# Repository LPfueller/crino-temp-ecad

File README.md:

View this project on [CADLAB.io](https://cadlab.io/project/27832). 

# Crino Board - Template (RevB.1.0)

Crino offers precise characterisations of lithium ion cells for quality control in battery manufacturing and research using the *crino instrument*. Every crino instrument consists of several *crino boards* with actuators and sensors that are connected to a central control system (currently a *Raspberry Pi*). This control system is performing all measurements and also provides a user interface to interact with the system. This repository consists of Kicad development files for the *board-template*. All *crino boards* should be derived from this template. 

## Project directory structure

- **docs**: Contains additional documentation of the project.
- **hardware**: Contains the KiCad project.
- **hardware/fab**: Contains automatically generated BOM, and gerber files.
- **simulation**: Contains LTSpice simulations related to this project.

## Local Development Experience

**Prerequisites**:

If you are new to `crino development workflow`, please visit [crino-onboarding](https://github.com/crinolab/crino-onboarding) and [crino-onboarding-ecad](https://github.com/crinolab/crino-onboarding-ecad/tree/master/ecad) first.

**How to use the Template**:

Open Kicad, create a `new Project by Template`. Navigate to the following path and select the *Board Template*. Create a new project with the selected template.

- `<your path>crino-repos/crino-board/ecad/hardware`

In order to update the schematics, the newly created project has to be linked to the template. Use [git submodules](https://git-scm.com/book/en/v2/Git-Tools-Submodules) to link this repository to your task specific crino-board.

- `git submodule add -f https://github.com/crinolab/crino-board.git ./ecad/hardware/crino-board`

If you want to update you task specific crino-board to a new template, use 

- `git submodule update --init --recursive`

Open Kicad again and switch to the schematics of your new project. A block called `mcu` should be visible. Enter the properties dialog and change the *sheet name* to the following path.

- `.\crino-board\ecad\hardware\mcu.sch`

Now the schematics are linked to the template project. Appending all the symbols may be necessary. 

**How to apply changes in the Layout**

in order to apply changes in the Layout. The [KiCad Action Plugins](https://github.com/MitjaNemec/Kicad_action_plugins) have to be installed. Follow the instructions on the website.  

**Workflow for the Plugin (Rev1)**

1. After updating the submodule open the template folder
2. Open the template-layout and select TP14 (Reference Point)
3. `Tools -> External Plugins -> Save/Restore Layout -> Save Layout`
4. Select `mcu.sch` in the window and save `mcu.pckl`
5. Close template layout without saving
6. Open `mcu.pckl` and change Row `5720` 

7. Open project and inspect the schematics
8. Open layout and note position of TP14
9. Delete all footprints and fracks of the template part
10. Start `Update PCB` and place the Footprints anywhere
11. Place TP14 at noted position and select it
12. `Tools -> External Plugins -> Save/Restore Layout -> Restore Layout`
13. Select `mcu.pckl` and wait until completed
14. Start DRC and correct errors
15. Save the Layout
16. Delete `mcu.pckl`

## General Components

The Template is the successor of the previously used [ESP32-POE-ISO](https://www.olimex.com/Products/IoT/ESP32/ESP32-POE-ISO/open-source-hardware). It contains all needed components of the board. 

**Basic Blocks**

The following blocks are present in the schematics:

- `poe` - Power over Ethernet controller
- `power` - Power supply for microcontroller (3.3V, 5V, 12V)
- `esp32` - [Microcontroller](https://www.espressif.com/sites/default/files/documentation/esp32-wroom-32e_esp32-wroom-32ue_datasheet_en.pdf) and programming interface  
- `ethernet` - Ethernet controller
- `io` - Pinout for derived boards

> Before you start making changes, please read the [development workflow](./docs/development-workflow.md) for Crino Power Board.

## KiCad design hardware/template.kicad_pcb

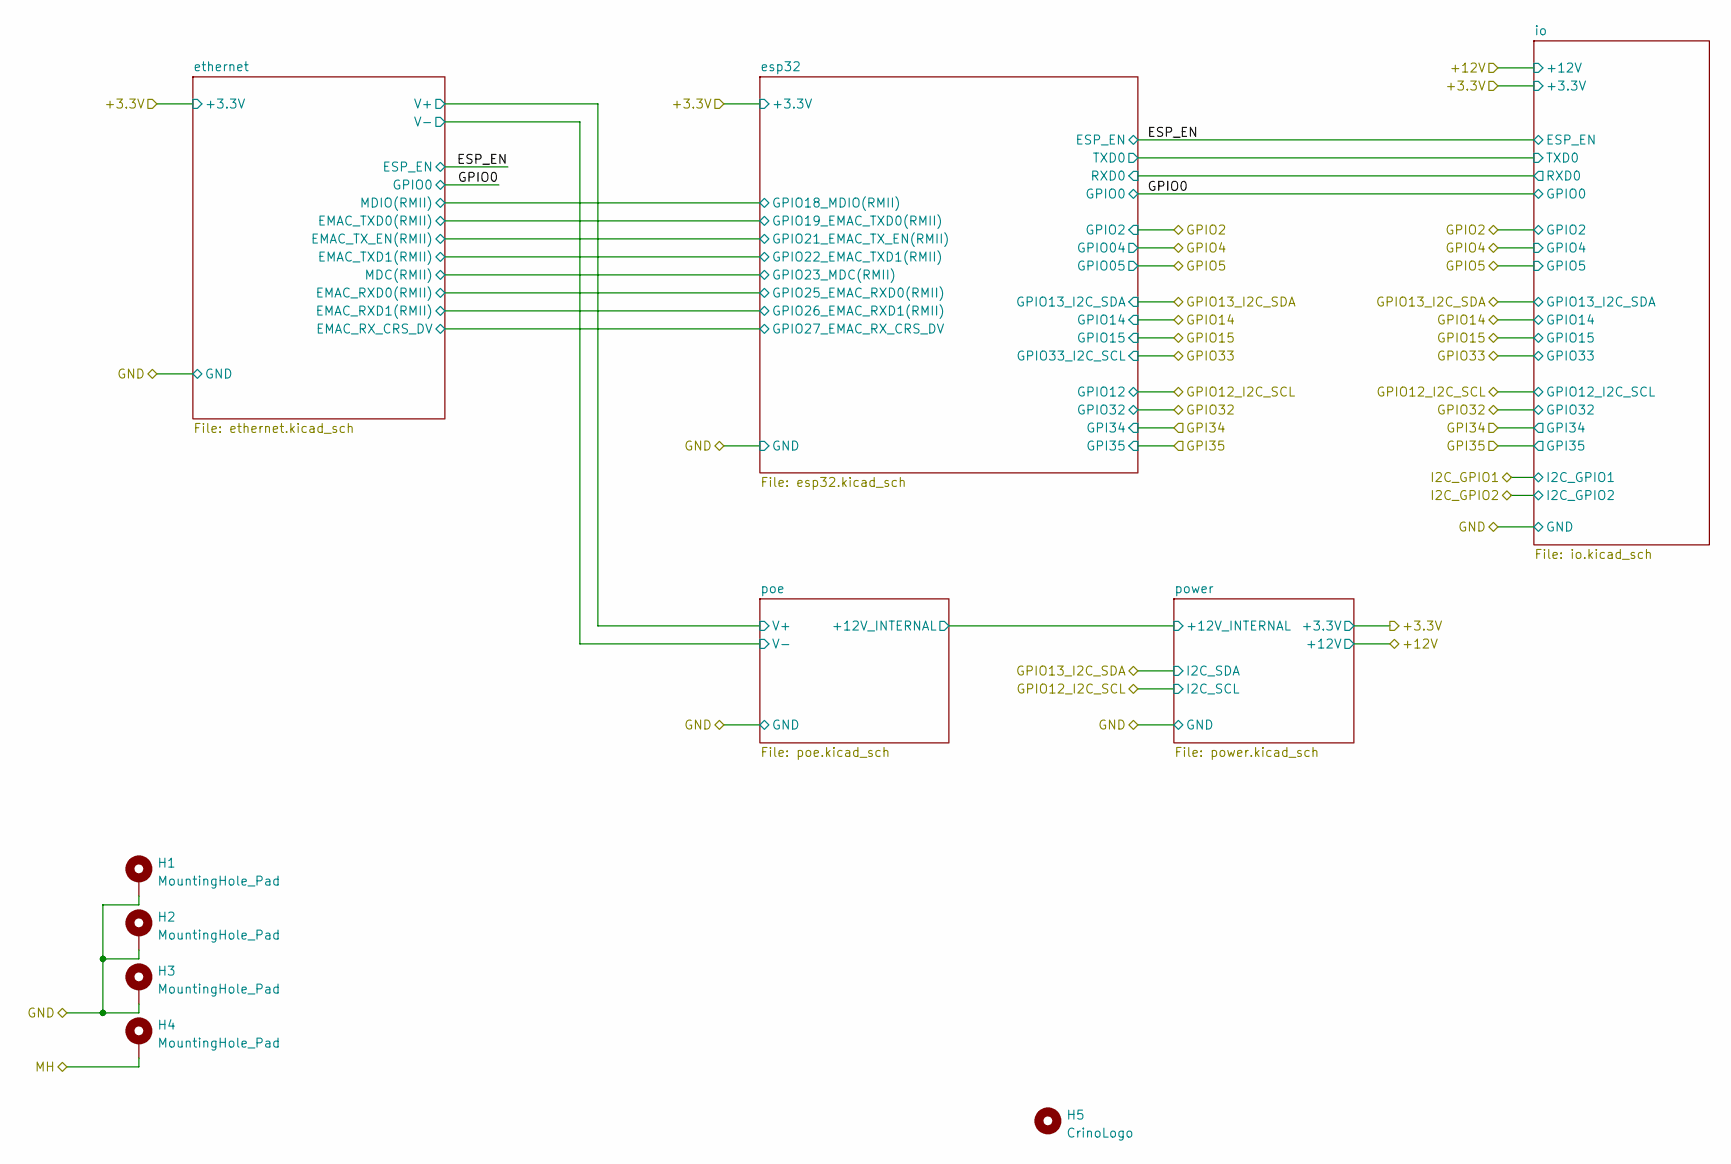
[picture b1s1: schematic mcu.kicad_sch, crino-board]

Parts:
H1, H2, H3, H4: MountingHole_Pad; MountingHole_3.2mm_M3_DIN965_Pad
H5: CrinoLogo; crino_logo

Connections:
/mcu/GND: H1.1, H2.1, H3.1; also elsewhere on the board
/mcu/MH: H4.1

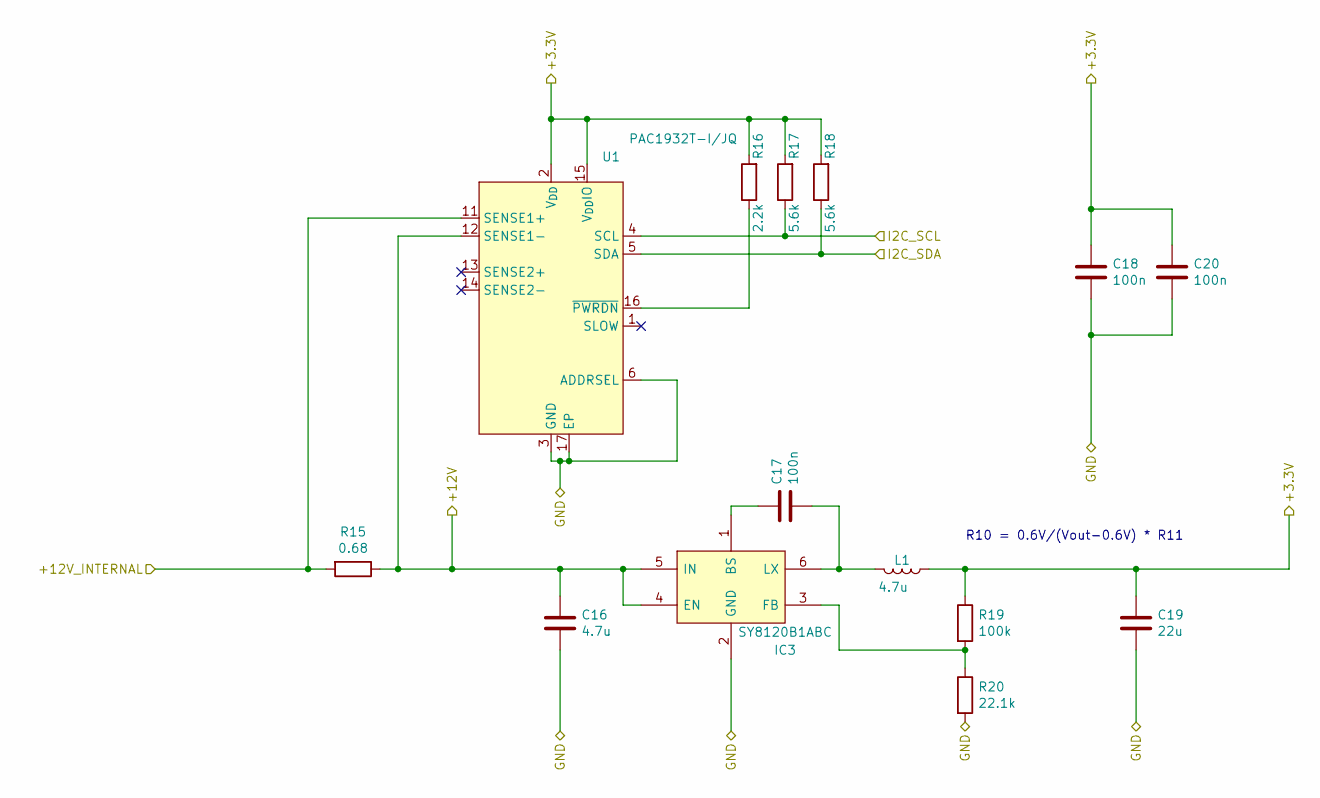
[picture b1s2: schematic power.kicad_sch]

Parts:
C16: 4.7u; C_0603_1608Metric; Manufacturer_Part_Number CL10A475KO8NNNC; jlc C19666
C17: 100n; C_0805_2012Metric; Manufacturer_Part_Number CL21B104KCFNNNE; jlc C28233
C18, C20: 100n; C_0603_1608Metric; Manufacturer_Part_Number CC0603KRX7R9BB104; jlc C14663
C19: 22u; C_1206_3216Metric; Manufacturer_Part_Number CL31A226KOHNNNE; jlc C90146
IC3: SY8120B1ABC; SOT-23-6; Manufacturer_Part_Number SY8120IABC; jlc C479076
L1: 4.7u; L_4.2x4.2_H2; Manufacturer_Part_Number SLW4020S4R7MST; jlc C206288
R15: 0.68; R_0805_2012Metric; Manufacturer_Part_Number SR732ATTDR680F; jlc C186593
R16: 2.2k; R_0603_1608Metric; Manufacturer_Part_Number 0603WAF2201T5E; jlc C4190
R17, R18: 5.6k; R_0603_1608Metric; Manufacturer_Part_Number 0603WAF5601T5E; jlc C23189
R19: 100k; R_0603_1608Metric; Manufacturer_Part_Number 0603WAF1003T5E; jlc C25803
R20: 22.1k; R_0603_1608Metric; Manufacturer_Part_Number 0603WAF2212T5E; jlc C25961
U1: PAC1932T-I/JQ; UQFN-16-1EP_4x4mm_P0.65mm_EP2.6x2.6mm; Manufacturer_Part_Number PAC1932T-I/JQ; jlc C623958

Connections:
/mcu/+3.3V: C18.1, C19.1, C20.1, L1.1, R16.2, R17.2, R18.2, R19.1, U1.2 (V_{DD}), U1.15 (V_{DD}IO); also elsewhere on the board
/mcu/+12V: C16.1, IC3.4 (EN), IC3.5 (IN), R15.1, U1.12 (SENSE1-); also elsewhere on the board
/mcu/GND: C16.2, C18.2, C19.2, C20.2, IC3.2 (GND), R20.2, U1.3 (GND), U1.6 (ADDRSEL), U1.7 (GND), U1.8 (GND), U1.9 (GND), U1.10 (GND), U1.17 (EP); also elsewhere on the board
/mcu/GPIO12_I2C_SCL: R17.1, U1.4 (SCL); also elsewhere on the board
/mcu/GPIO13_I2C_SDA: R18.1, U1.5 (SDA); also elsewhere on the board
/mcu/poe/+12V_INTERNAL: R15.2, U1.11 (SENSE1+); also elsewhere on the board
unnamed: C17.1, IC3.1 (BS)
unnamed: C17.2, IC3.6 (LX), L1.2
unnamed: IC3.3 (FB), R19.2, R20.1
unnamed: R16.1, U1.16 (~PWRDN)

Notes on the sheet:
R10 = 0.6V/(Vout-0.6V) * R11

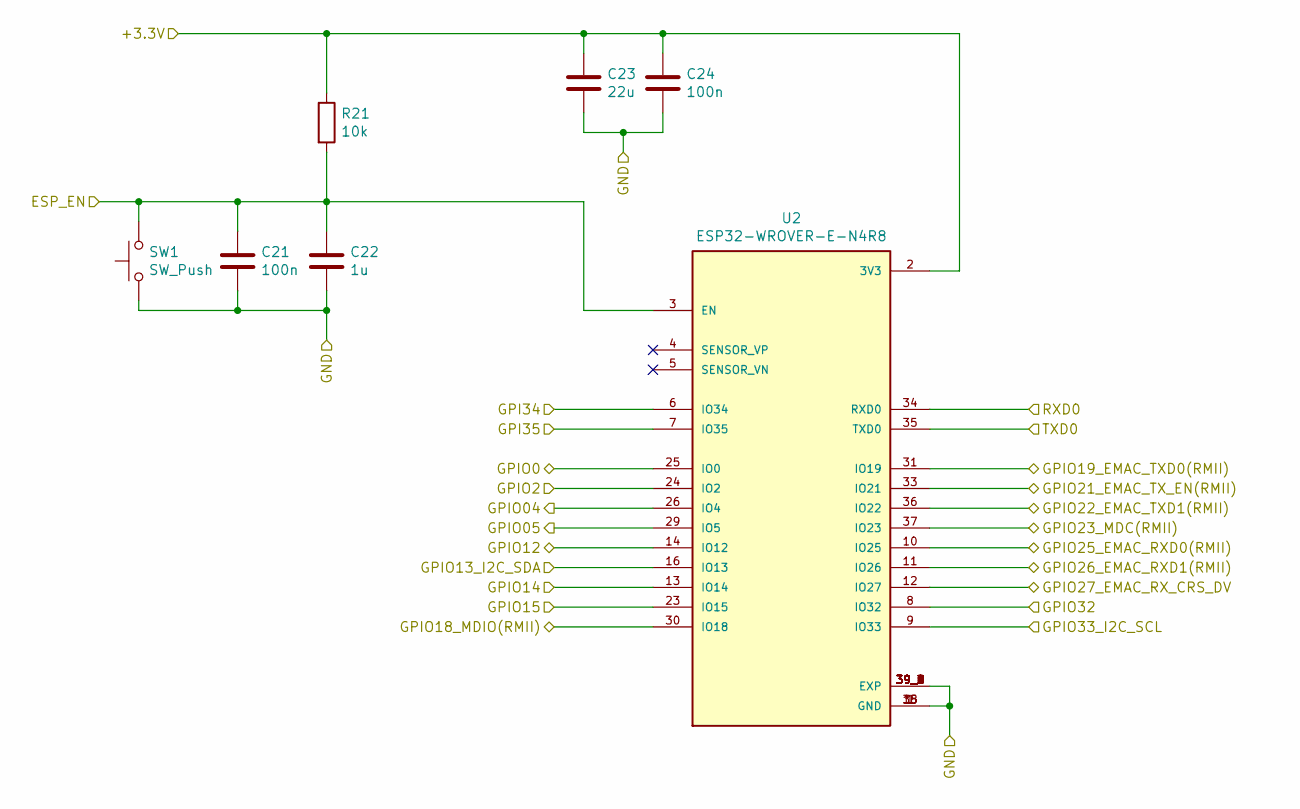
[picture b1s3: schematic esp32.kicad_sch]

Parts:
C21: 100n; C_0805_2012Metric; Manufacturer_Part_Number CL21B104KCFNNNE; jlc C28233
C22: 1u; C_0603_1608Metric; Manufacturer_Part_Number CL10A105KB8NNNC; jlc C15849
C23: 22u; C_0603_1608Metric; Manufacturer_Part_Number CL10A226MQ8NRNC; jlc C59461
C24: 100n; C_0603_1608Metric; Manufacturer_Part_Number CC0603KRX7R9BB104; jlc C14663
R21: 10k; R_0603_1608Metric; Manufacturer_Part_Number 0603WAF1002T5E; jlc C25804
SW1: SW_Push; SW_TS-1187A-B-A-B; Manufacturer_Part_Number TS-1187A-B-A-B; jlc C318884
U2: ESP32-WROVER-E-N4R8; PARTREV 1.6; jlc C967023

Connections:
/mcu/+3.3V: C23.1, C24.1, R21.1, U2.2 (3V3); also elsewhere on the board
/mcu/ESP_EN: C21.1, C22.1, R21.2, SW1.2, U2.3 (EN); also elsewhere on the board
/mcu/GND: C21.2, C22.2, C23.2, C24.2, SW1.1, U2.1 (GND), U2.15 (GND), U2.38 (GND), U2.39_1 (EXP), U2.39_2 (EXP), U2.39_3 (EXP), U2.39_4 (EXP), U2.39_5 (EXP), U2.39_6 (EXP), U2.39_7 (EXP), U2.39_8 (EXP), U2.39_9 (EXP); also elsewhere on the board
/mcu/GPI34: U2.6 (IO34); also elsewhere on the board
/mcu/GPI35: U2.7 (IO35); also elsewhere on the board
/mcu/GPIO0: U2.25 (IO0); also elsewhere on the board
/mcu/GPIO2: U2.24 (IO2); also elsewhere on the board
/mcu/GPIO4: U2.26 (IO4); also elsewhere on the board
/mcu/GPIO5: U2.29 (IO5); also elsewhere on the board
/mcu/GPIO12_I2C_SCL: U2.14 (IO12); also elsewhere on the board
/mcu/GPIO13_I2C_SDA: U2.16 (IO13); also elsewhere on the board
/mcu/GPIO14: U2.13 (IO14); also elsewhere on the board
/mcu/GPIO15: U2.23 (IO15); also elsewhere on the board
/mcu/GPIO32: U2.8 (IO32); also elsewhere on the board
/mcu/GPIO33: U2.9 (IO33); also elsewhere on the board
/mcu/esp32/GPIO18_MDIO(RMII): U2.30 (IO18); also elsewhere on the board
/mcu/esp32/GPIO19_EMAC_TXD0(RMII): U2.31 (IO19); also elsewhere on the board
/mcu/esp32/GPIO21_EMAC_TX_EN(RMII): U2.33 (IO21); also elsewhere on the board
/mcu/esp32/GPIO22_EMAC_TXD1(RMII): U2.36 (IO22); also elsewhere on the board
/mcu/esp32/GPIO23_MDC(RMII): U2.37 (IO23); also elsewhere on the board
/mcu/esp32/GPIO25_EMAC_RXD0(RMII): U2.10 (IO25); also elsewhere on the board
/mcu/esp32/GPIO26_EMAC_RXD1(RMII): U2.11 (IO26); also elsewhere on the board
/mcu/esp32/GPIO27_EMAC_RX_CRS_DV: U2.12 (IO27); also elsewhere on the board
/mcu/esp32/RXD0: U2.34 (RXD0); also elsewhere on the board
/mcu/esp32/TXD0: U2.35 (TXD0); also elsewhere on the board

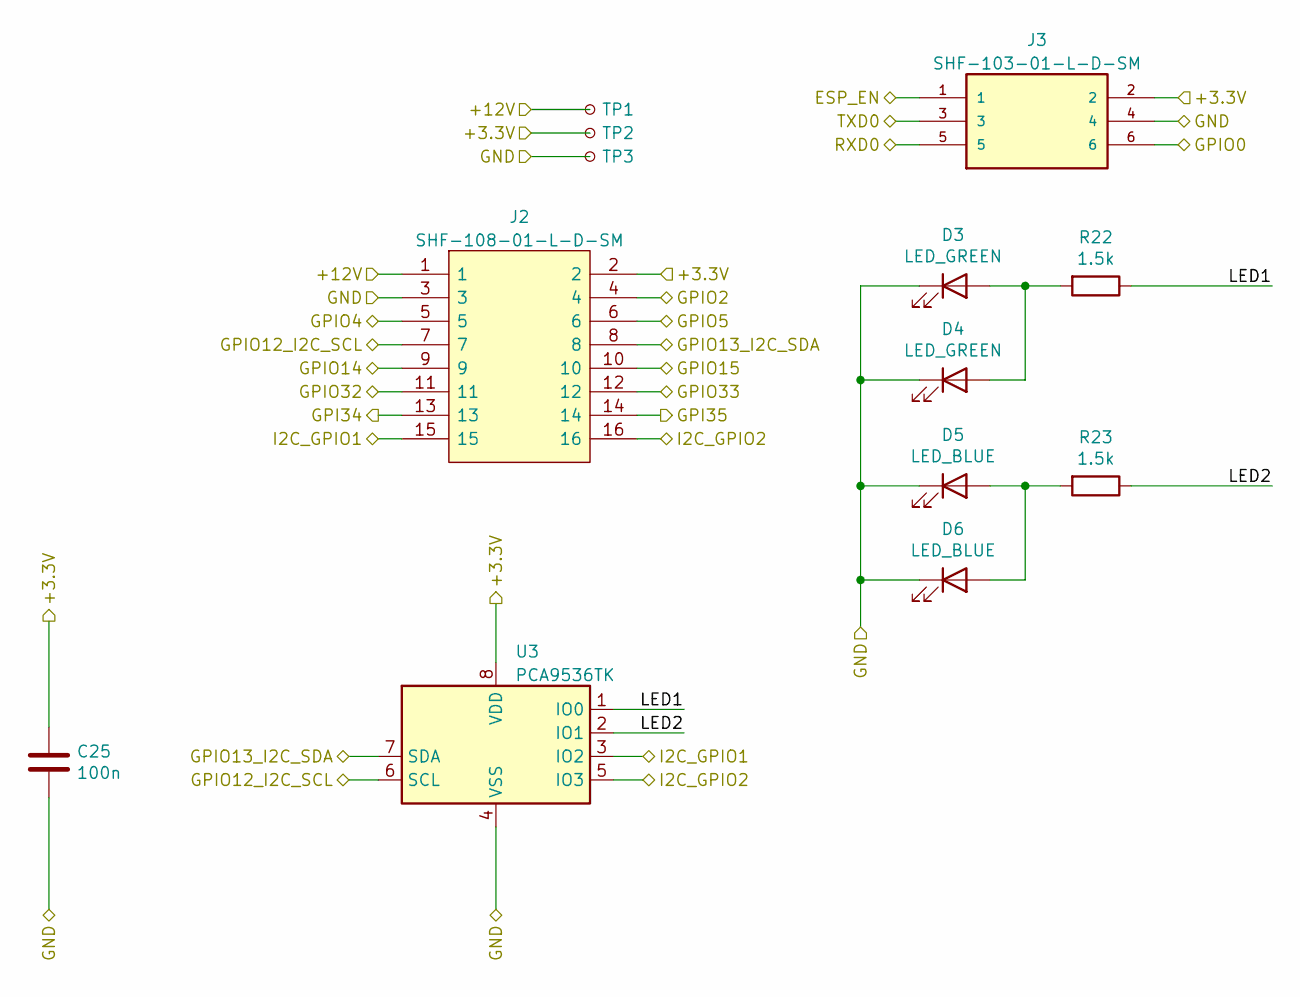
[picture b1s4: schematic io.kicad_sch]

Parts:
C25: 100n; C_0603_1608Metric; Manufacturer_Part_Number CC0603KRX7R9BB104; jlc C14663
D3, D4: LED_GREEN; LED_3210Metric_Right_Angle; Manufacturer_Part_Number TJ-S3210SW5TGLC2G-A5; jlc C273630
D5, D6: LED_BLUE; LED_3210Metric_Right_Angle; Manufacturer_Part_Number TJ-S3210SW5TGLC6B-A5; jlc C273631
J2: SHF-108-01-L-D-SM; SHF-108-01-X-D-SM; Manufacturer_Part_Number SHF-108-01-L-D-SM; Mouser Part Number 200-SHF10801LDSM
J3: SHF-103-01-L-D-SM; SAMTEC_SHF-103-01-L-D-SM; PARTREV R
R22, R23: 1.5k; R_0603_1608Metric; Manufacturer_Part_Number 0603WAF1501T5E; jlc C22843
TP1: 12V; TestPoint_Pad_D2.0mm
TP2: 3.3V; TestPoint_Pad_D2.0mm
TP3: GND; TestPoint_Pad_D2.0mm
U3: PCA9536TK; SON50P300X300X100-9N-D; Manufacturer_Part_Number PCA9536TK,118; jlc C2652283

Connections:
/mcu/+3.3V: C25.1, J2.2, J3.2, TP2.1, U3.8 (VDD); also elsewhere on the board
/mcu/+12V: J2.1, TP1.1; also elsewhere on the board
/mcu/ESP_EN: J3.1; also elsewhere on the board
/mcu/GND: C25.2, D3.1 (K), D4.1 (K), D5.1 (K), D6.1 (K), J2.3, J3.4, TP3.1, U3.4 (VSS); also elsewhere on the board
/mcu/GPI34: J2.13; also elsewhere on the board
/mcu/GPI35: J2.14; also elsewhere on the board
/mcu/GPIO0: J3.6; also elsewhere on the board
/mcu/GPIO2: J2.4; also elsewhere on the board
/mcu/GPIO4: J2.5; also elsewhere on the board
/mcu/GPIO5: J2.6; also elsewhere on the board
/mcu/GPIO12_I2C_SCL: J2.7, U3.6 (SCL); also elsewhere on the board
/mcu/GPIO13_I2C_SDA: J2.8, U3.7 (SDA); also elsewhere on the board
/mcu/GPIO14: J2.9; also elsewhere on the board
/mcu/GPIO15: J2.10; also elsewhere on the board
/mcu/GPIO32: J2.11; also elsewhere on the board
/mcu/GPIO33: J2.12; also elsewhere on the board
/mcu/I2C_GPIO1: J2.15, U3.3 (IO2)
/mcu/I2C_GPIO2: J2.16, U3.5 (IO3)
/mcu/esp32/RXD0: J3.5; also elsewhere on the board
/mcu/esp32/TXD0: J3.3; also elsewhere on the board
/mcu/io/LED1: R22.1, U3.1 (IO0)
/mcu/io/LED2: R23.1, U3.2 (IO1)
unnamed: D3.2 (A), D4.2 (A), R22.2
unnamed: D5.2 (A), D6.2 (A), R23.2

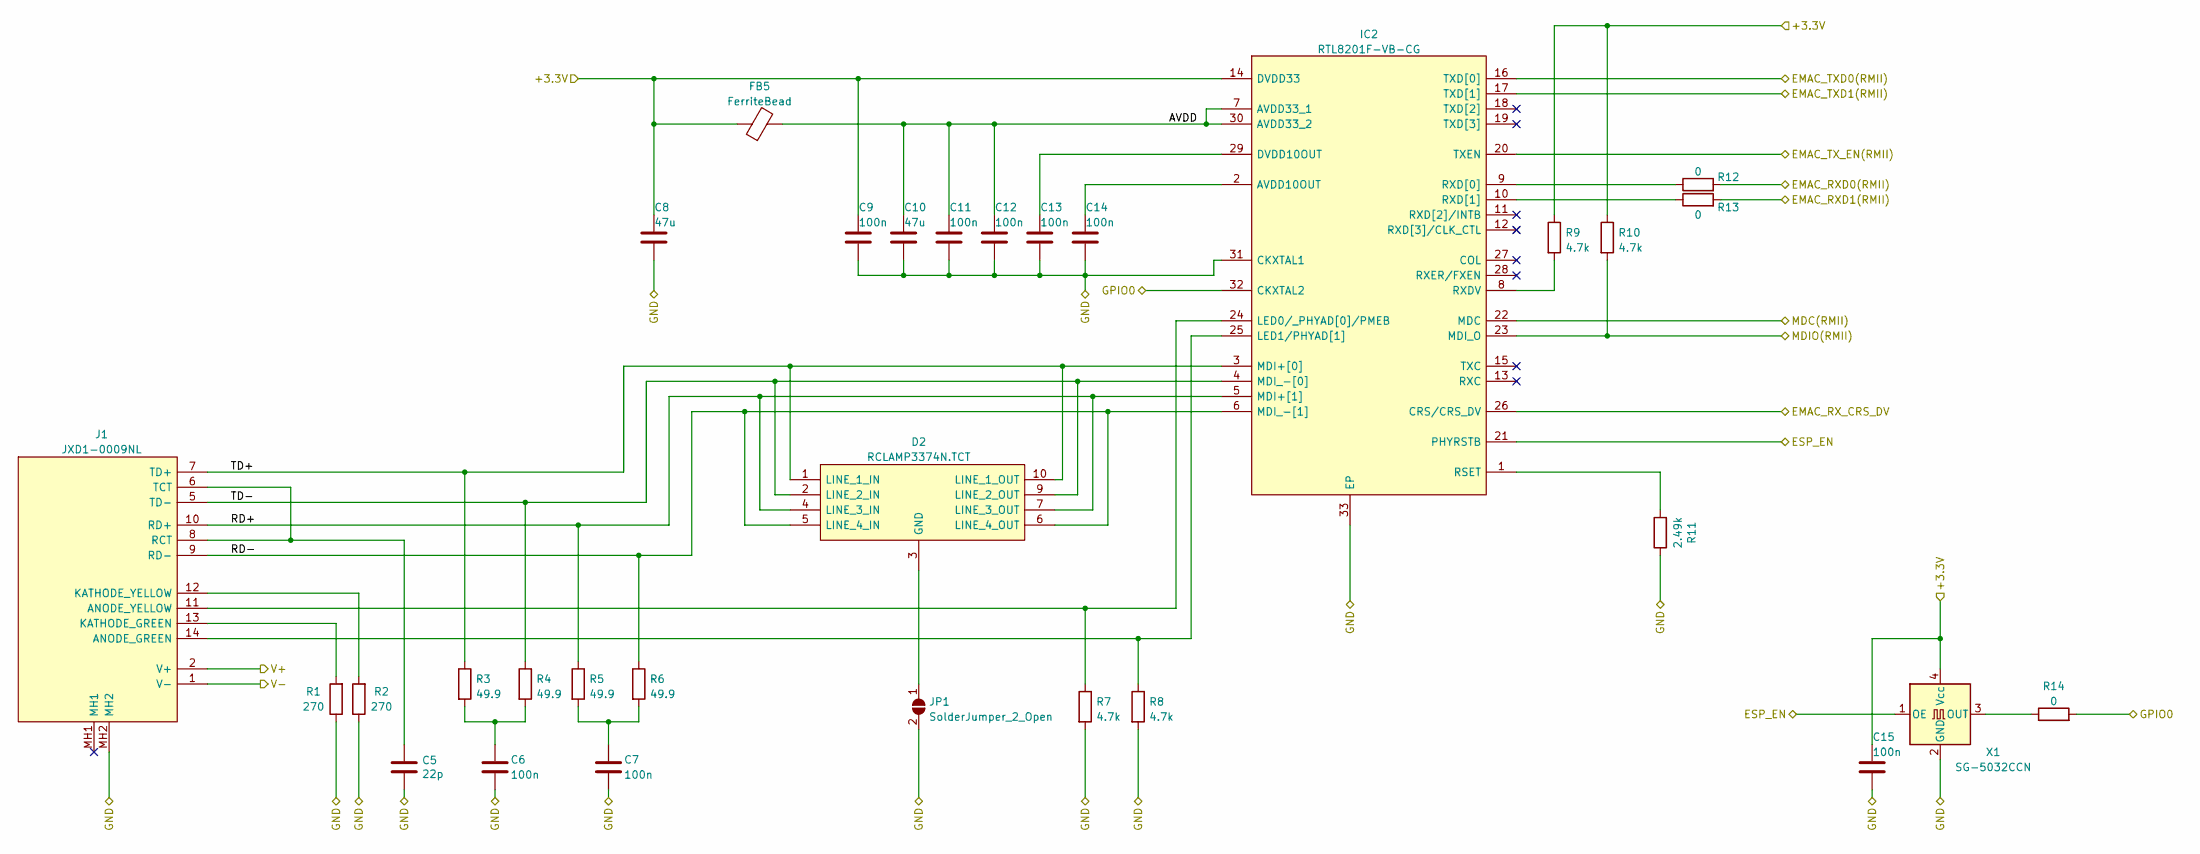
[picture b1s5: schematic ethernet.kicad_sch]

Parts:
C5: 22p; C_0603_1608Metric; Manufacturer_Part_Number CL10C220JB8NNNC; jlc C1653
C6, C7, C9, C11, C12, C13, C14, C15: 100n; C_0603_1608Metric; Manufacturer_Part_Number CC0603KRX7R9BB104; jlc C14663
C8, C10: 47u; C_0603_1608Metric; Manufacturer_Part_Number CL10A476MQ8QRNC; jlc C730416
D2: RCLAMP3374N.TCT; RCLAMP3374NTCT; Manufacturer_Part_Number TPRCLAMP3374N; Mouser Part Number 947-RCLAMP3374N.TCT
FB5: FerriteBead; L_0805_2012Metric; Manufacturer_Part_Number UPZ2012E601-2R0TF; jlc C98308
IC2: RTL8201F-VB-CG; QFN-32-1EP_5x5mm_P0.5mm_EP3.6x3.6mm_ThermalVias; Manufacturer_Part_Number RTL8201F-VB-CG; jlc C45044
J1: JXD1-0009NL; JXD10009NL; Manufacturer_Part_Number JXD1-0009NL; Mouser Part Number 673-JXD1-0009NL
JP1: SolderJumper_2_Open; SolderJumper-2_P1.3mm_Open_RoundedPad1.0x1.5mm
R1, R2: 270; R_0603_1608Metric; Manufacturer_Part_Number 0603WAF2700T5E; jlc C22966
R3, R4, R5, R6: 49.9; R_0603_1608Metric; Manufacturer_Part_Number 0603WAF499JT5E; jlc C23185
R7, R8, R9, R10: 4.7k; R_0603_1608Metric; Manufacturer_Part_Number 0603WAF4701T5E; jlc C23162
R11: 2.49k; R_0603_1608Metric; Manufacturer_Part_Number 0603WAF2491T5E; jlc C22908
R12, R13, R14: 0; R_0603_1608Metric; Manufacturer_Part_Number 0603WAF0000T5E; jlc C21189
X1: SG-5032CCN; Oscillator_SMD_SeikoEpson_SG8002LB-4Pin_5.0x3.2mm; Manufacturer_Part_Number S5D50.000000B20F30T; jlc C387308

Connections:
/mcu/+3.3V: C8.1, C9.1, C15.1, FB5.1, IC2.14 (DVDD33), R9.1, R10.1, X1.4 (Vcc); also elsewhere on the board
/mcu/ESP_EN: IC2.21 (PHYRSTB), X1.1 (OE); also elsewhere on the board
/mcu/GND: C5.2, C6.2, C7.2, C8.2, C9.2, C10.2, C11.2, C12.2, C13.2, C14.2, C15.2, IC2.31 (CKXTAL1), IC2.33 (EP), J1.MH2, JP1.2 (B), R1.1, R2.1, R7.2, R8.2, R11.1, X1.2 (GND); also elsewhere on the board
/mcu/GPIO0: IC2.32 (CKXTAL2), R14.2; also elsewhere on the board
/mcu/esp32/GPIO18_MDIO(RMII): IC2.23 (MDI_O), R10.2; also elsewhere on the board
/mcu/esp32/GPIO19_EMAC_TXD0(RMII): IC2.16 (TXD[0]); also elsewhere on the board
/mcu/esp32/GPIO21_EMAC_TX_EN(RMII): IC2.20 (TXEN); also elsewhere on the board
/mcu/esp32/GPIO22_EMAC_TXD1(RMII): IC2.17 (TXD[1]); also elsewhere on the board
/mcu/esp32/GPIO23_MDC(RMII): IC2.22 (MDC); also elsewhere on the board
/mcu/esp32/GPIO25_EMAC_RXD0(RMII): R12.2; also elsewhere on the board
/mcu/esp32/GPIO26_EMAC_RXD1(RMII): R13.2; also elsewhere on the board
/mcu/esp32/GPIO27_EMAC_RX_CRS_DV: IC2.26 (CRS/CRS_DV); also elsewhere on the board
/mcu/ethernet/AVDD: C10.1, C11.1, C12.1, FB5.2, IC2.7 (AVDD33_1), IC2.30 (AVDD33_2)
/mcu/ethernet/RD+: D2.4 (LINE_3_IN), D2.7 (LINE_3_OUT), IC2.5 (MDI+[1]), J1.10 (RD+), R5.1
/mcu/ethernet/RD-: D2.5 (LINE_4_IN), D2.6 (LINE_4_OUT), IC2.6 (MDI_-[1]), J1.9 (RD-), R6.1
/mcu/ethernet/TD+: D2.1 (LINE_1_IN), D2.10 (LINE_1_OUT), IC2.3 (MDI+[0]), J1.7 (TD+), R3.1
/mcu/ethernet/TD-: D2.2 (LINE_2_IN), D2.9 (LINE_2_OUT), IC2.4 (MDI_-[0]), J1.5 (TD-), R4.1
/mcu/ethernet/V+: J1.2 (V+); also elsewhere on the board
/mcu/ethernet/V-: J1.1 (V-); also elsewhere on the board
unnamed: C5.1, J1.6 (TCT), J1.8 (RCT)
unnamed: C6.1, R3.2, R4.2
unnamed: C7.1, R5.2, R6.2
unnamed: C13.1, IC2.29 (DVDD10OUT)
unnamed: C14.1, IC2.2 (AVDD10OUT)
unnamed: D2.3 (GND), D2.8 (GND), D2.12 (GND), JP1.1 (A)
unnamed: IC2.1 (RSET), R11.2
unnamed: IC2.8 (RXDV), R9.2
unnamed: IC2.9 (RXD[0]), R12.1
unnamed: IC2.10 (RXD[1]), R13.1
unnamed: IC2.24 (LED0/_PHYAD[0]/PMEB), J1.11 (ANODE_YELLOW), R7.1
unnamed: IC2.25 (LED1/PHYAD[1]), J1.14 (ANODE_GREEN), R8.1
unnamed: J1.12 (KATHODE_YELLOW), R2.2
unnamed: J1.13 (KATHODE_GREEN), R1.2
unnamed: R14.1, X1.3 (OUT)

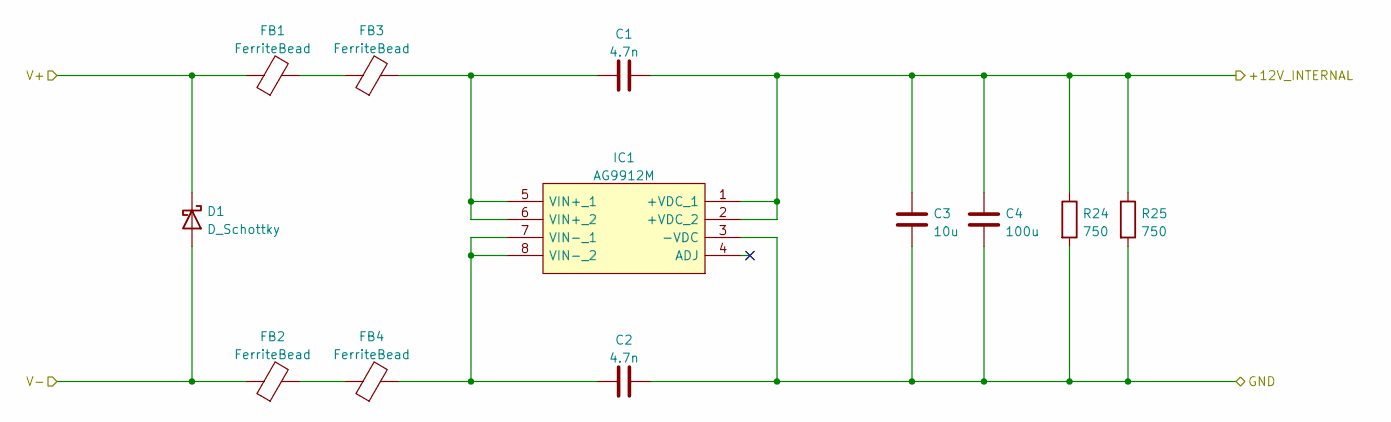
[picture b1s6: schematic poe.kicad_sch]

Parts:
C1, C2: 4.7n; C_1206_3216Metric; Manufacturer_Part_Number 1206B472K202NT; jlc C41017
C3: 10u; C_0805_2012Metric; Manufacturer_Part_Number GRM21BR61E106KA73L; jlc C84416
C4: 100u; CP_Elec_5x5.4; Manufacturer_Part_Number RVT1E100M0505; jlc C86604
D1: D_Schottky; D_SMA; Manufacturer_Part_Number SMAJ58A-TP; jlc C669036
FB1, FB2, FB3, FB4: FerriteBead; L_1206_3216Metric; Manufacturer_Part_Number BLM31KN102SN1L; jlc C560056
IC1: AG9912M; Mouser Part Number 480-AG9912M
R24, R25: 750; R_0805_2012Metric; Manufacturer_Part_Number ERJP06F7500V; jlc C441980

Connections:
/mcu/GND: C2.2, C3.2, C4.2, IC1.3 (-VDC), R24.2, R25.2; also elsewhere on the board
/mcu/ethernet/V+: D1.1 (K), FB1.1; also elsewhere on the board
/mcu/ethernet/V-: D1.2 (A), FB2.1; also elsewhere on the board
/mcu/poe/+12V_INTERNAL: C1.2, C3.1, C4.1, IC1.1 (+VDC_1), IC1.2 (+VDC_2), R24.1, R25.1; also elsewhere on the board
unnamed: C1.1, FB3.2, IC1.5 (VIN+_1), IC1.6 (VIN+_2)
unnamed: C2.1, FB4.2, IC1.7 (VIN-_1), IC1.8 (VIN-_2)
unnamed: FB1.2, FB3.1
unnamed: FB2.2, FB4.1

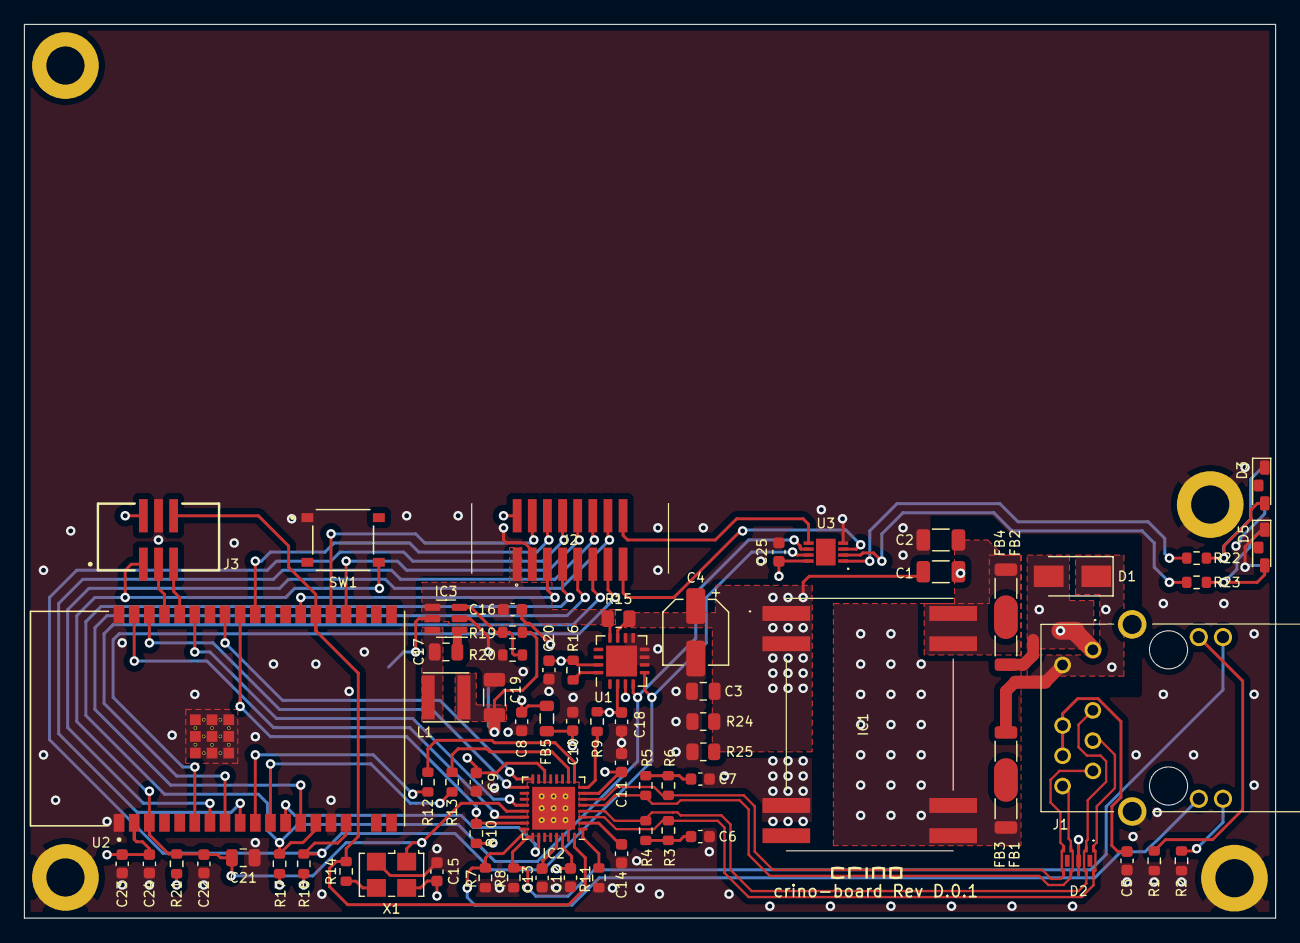
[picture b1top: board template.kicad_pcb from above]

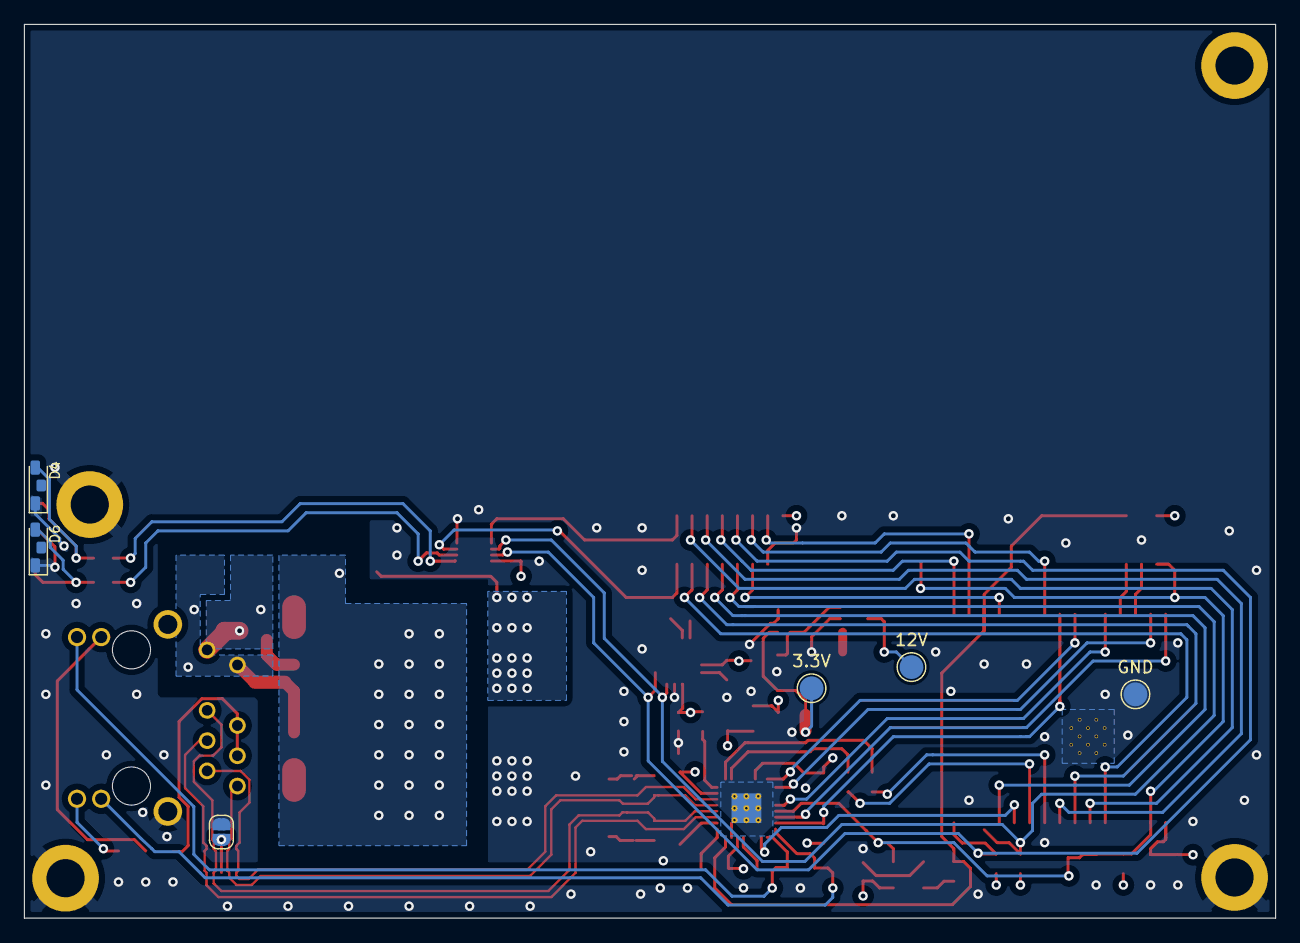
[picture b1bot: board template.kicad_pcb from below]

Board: 4 copper layers, 105.0 x 75.0 mm, 82 parts (6 on the bottom side), 63 nets.
